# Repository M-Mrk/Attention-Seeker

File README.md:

# Attention-Seeker
## Overview
A multifunctional desk peripheral designed to display and alert you to notifications.

Attention-Seeker receives notifications from a companion app and displays them on its 2.8" color screen, with optional visual and audible alerts. It also features a rotary encoder and three mechanical keyboard switches for user input (no touch!).

In addition to notification-related features, it functions as a **clock**, **desk light**, and **macropad**.

### Why?
I often missed important notifications while zoning out or concentrating and also needed a desk light, so I built this.

### How?
- 2.8" TFT screen
- 3 mechanical keyboard switches
- Rotary encoder
- Rigid LED filament
- Buzzer
- ESP32-S3 DevKitC N16R8 CP2102
- Python companion app to run on a PC

### Example Use Cases
- **Notification:** Attention-Seeker buzzes, blinks, and displays the message.
- **Desk Light:** Toggle and dim the built-in LED for illumination.

## Features

### Notifications
Displays incoming notifications sent by the companion app with optional blinking or buzzing.

### Clock
- Displays time
- Synced via the companion app

### Macropad
- 6 hotkeys

### Navigation
- Mechanical keyboard switches for on-page actions
- Rotary encoder for switching between pages

### Other Features
- Dimmable desk light
- Buzzer for alerts

## Hardware

### MCU
The ESP32-S3 might be overkill but is ideal for handling the screen's pixel density, enabling fast page switching. Almost all pins are utilized, as the SPI interface for the screen consumes the majority of them.

### Lighting

#### LED Filament
The 3V filament draws about 100mA, requiring a 5V-to-3.3V LDO for power. An N-channel MOSFET drives the negative side of the LED filament.

#### Backlight
The backlight's current draw was uncertain during PCB design, so a transistor was added between it and the MCU for safety. This transistor is pulled high and can only be pulled low by the MCU.

### Other Components
All remaining components (switches, encoder, buzzer) are directly connected to the MCU.

# Build it yourself
## PCB
Order the PCB from the gerberfiles in [this zip](pcb/production/Attention-Seeker.zip). I would recommend black and the CAD files are designed for a 1.6mm thick pcb.

## Parts
Get/Order all parts from the [BOM](BOM.csv). I ordered them from reichelt and aliexpress and have included links for them. Watch out when buying the esp32 devkit, as there are countless versions and some even claim to be something different than they are.

## Soldering
First solder all smd components on the back, then the devkit and buzzer. Now you can solder on the screen based on your screen you might have to remove the sd card slot or cover it in kapton tape to be sure. I didnt have to shorten any pins, but you might have to. At last you can solder the LED on, but be very careful it snaps easily.

## Case
Print both the [top](case/case-top.3mf) and [bottom](case/case-bottom.3mf). If you dont have a cover for the rotary encoder you can also print [this](case/knob.3mf).

Place the pcb in the bottom and press fit the top on.

# Companion App
## Setup
Download [this folder](software/non-embedded/). 
Install the dependencys (if you want in a virtual environment)

`pip install -r requirements.txt`

Then just start the app
`python3 main.py`

## Device selection
Press refresh and it should automatically select your esp32. If not go through the drop down and select it manually.

## Time syncing
Press Sync Time

## Notifications
It will automatically send notifications to the device, but you can test it yourself. Press on the arrow to the left to extend the menu. Enter all your test informations and press Send JSON Notification. It should show up on the device and play a tone.

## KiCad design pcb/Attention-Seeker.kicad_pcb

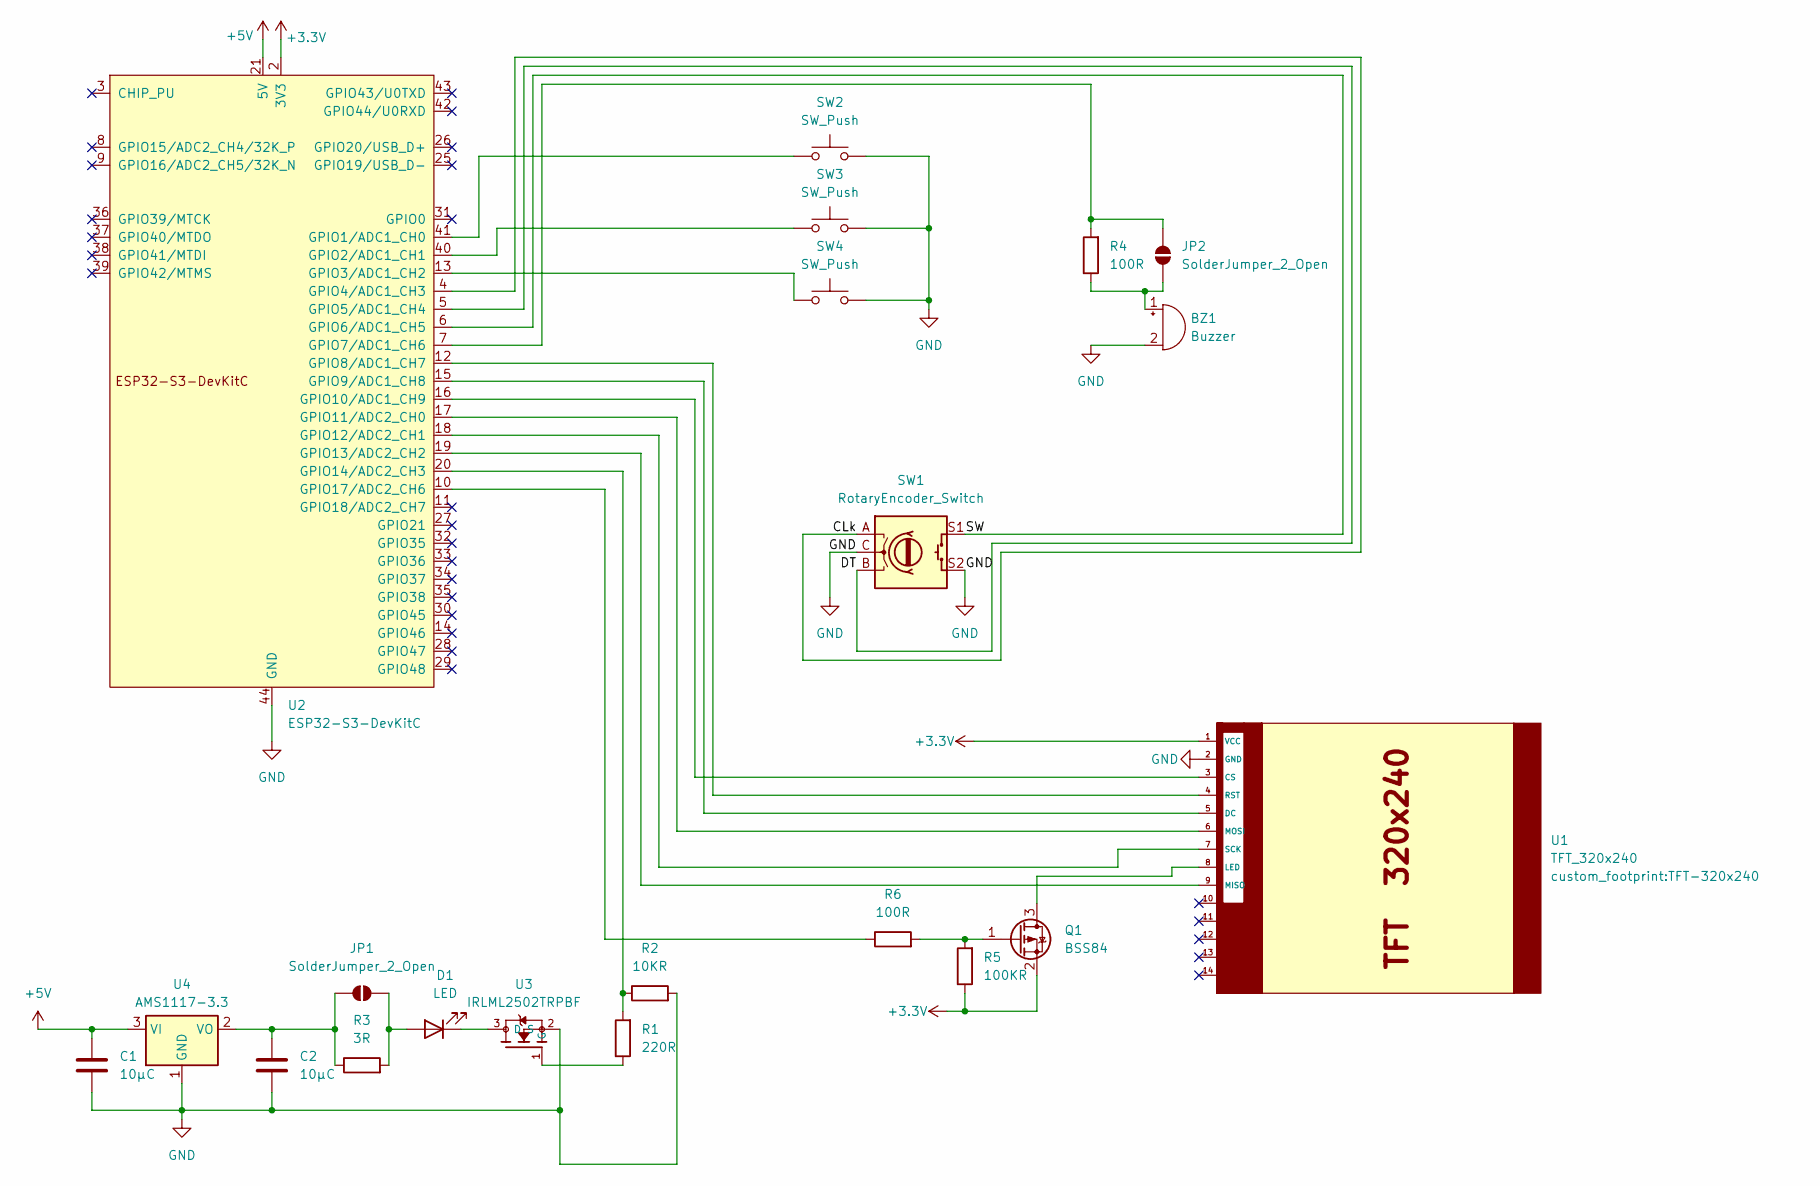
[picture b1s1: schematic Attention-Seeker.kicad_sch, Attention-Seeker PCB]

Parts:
BZ1: Buzzer; Buzzer_12x9.5RM7.6
C1, C2: 10µC; C_1206_3216Metric_Pad1.33x1.80mm_HandSolder
D1: LED; 38mm rigid LED filament
JP1, JP2: SolderJumper_2_Open; SolderJumper-2_P1.3mm_Open_Pad1.0x1.5mm
Q1: BSS84; SOT-23
R1: 220R; R_1206_3216Metric_Pad1.30x1.75mm_HandSolder
R2: 10KR; R_1206_3216Metric_Pad1.30x1.75mm_HandSolder
R3: 3R; R_1206_3216Metric_Pad1.30x1.75mm_HandSolder
R4, R6: 100R; R_1206_3216Metric_Pad1.30x1.75mm_HandSolder
R5: 100KR; R_1206_3216Metric_Pad1.30x1.75mm_HandSolder
SW1: RotaryEncoder_Switch; RotaryEncoder_Alps_EC11E-Switch_Vertical_H20mm
SW2, SW3, SW4: SW_Push; SW_Cherry_MX_1.00u_PCB
U1: TFT_320x240; TFT-320x240
U2: ESP32-S3-DevKitC
U3: IRLML2502TRPBF; SOT23
U4: AMS1117-3.3; SOT-223-3_TabPin2

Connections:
+3.3V: Q1.2 (S), R5.1, U1.1 (VCC), U2.1 (3V3), U2.2 (3V3)
+5V: C1.2, U2.21 (5V), U4.3 (VI)
/CLk: SW1.A, U2.4 (GPIO4/ADC1_CH3)
/DT: SW1.B, U2.5 (GPIO5/ADC1_CH4)
/SW: SW1.S1, U2.6 (GPIO6/ADC1_CH5)
GND: BZ1.2 (-), C1.1, C2.1, R2.2, SW1.C, SW1.S2, SW2.2, SW3.2, SW4.2, U1.2 (GND), U2.22 (GND), U2.23 (GND), U2.24 (GND), U2.44 (GND), U3.2 (S), U4.1 (GND)
unnamed: BZ1.1 (+), JP2.2 (B), R4.1
unnamed: D1.2 (A), JP1.2 (B), R3.2
unnamed: D1.1 (K), U3.3 (D)
unnamed: C2.2, JP1.1 (A), R3.1, U4.2 (VO)
unnamed: JP2.1 (A), R4.2, U2.7 (GPIO7/ADC1_CH6)
unnamed: Q1.3 (D), U1.8 (LED)
unnamed: Q1.1 (G), R5.2, R6.2
unnamed: U1.3 (CS), U2.16 (GPIO10/ADC1_CH9)
unnamed: U1.5 (DC), U2.15 (GPIO9/ADC1_CH8)
unnamed: U1.9 (MISO), U2.19 (GPIO13/ADC2_CH2)
unnamed: U1.6 (MOSI), U2.17 (GPIO11/ADC2_CH0)
unnamed: U1.4 (RST), U2.12 (GPIO8/ADC1_CH7)
unnamed: U1.7 (SCK), U2.18 (GPIO12/ADC2_CH1)
unnamed: SW2.1, U2.41 (GPIO1/ADC1_CH0)
unnamed: SW3.1, U2.40 (GPIO2/ADC1_CH1)
unnamed: SW4.1, U2.13 (GPIO3/ADC1_CH2)
unnamed: R1.2, R2.1, U2.20 (GPIO14/ADC2_CH3)
unnamed: R6.1, U2.10 (GPIO17/ADC2_CH6)
unnamed: R1.1, U3.1 (G)

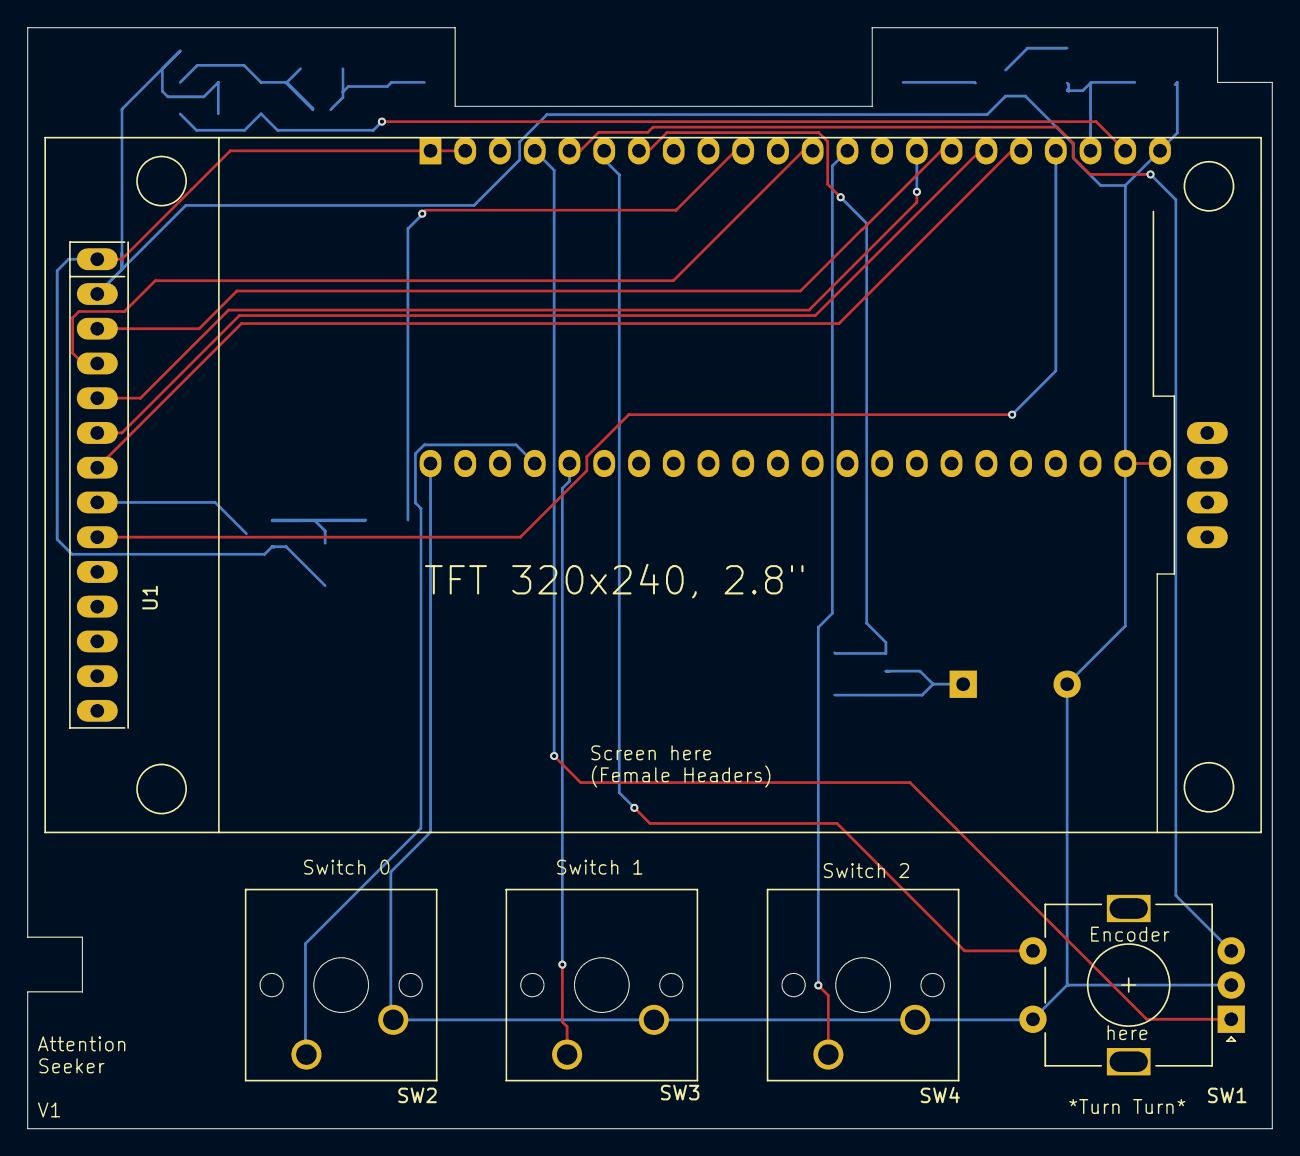
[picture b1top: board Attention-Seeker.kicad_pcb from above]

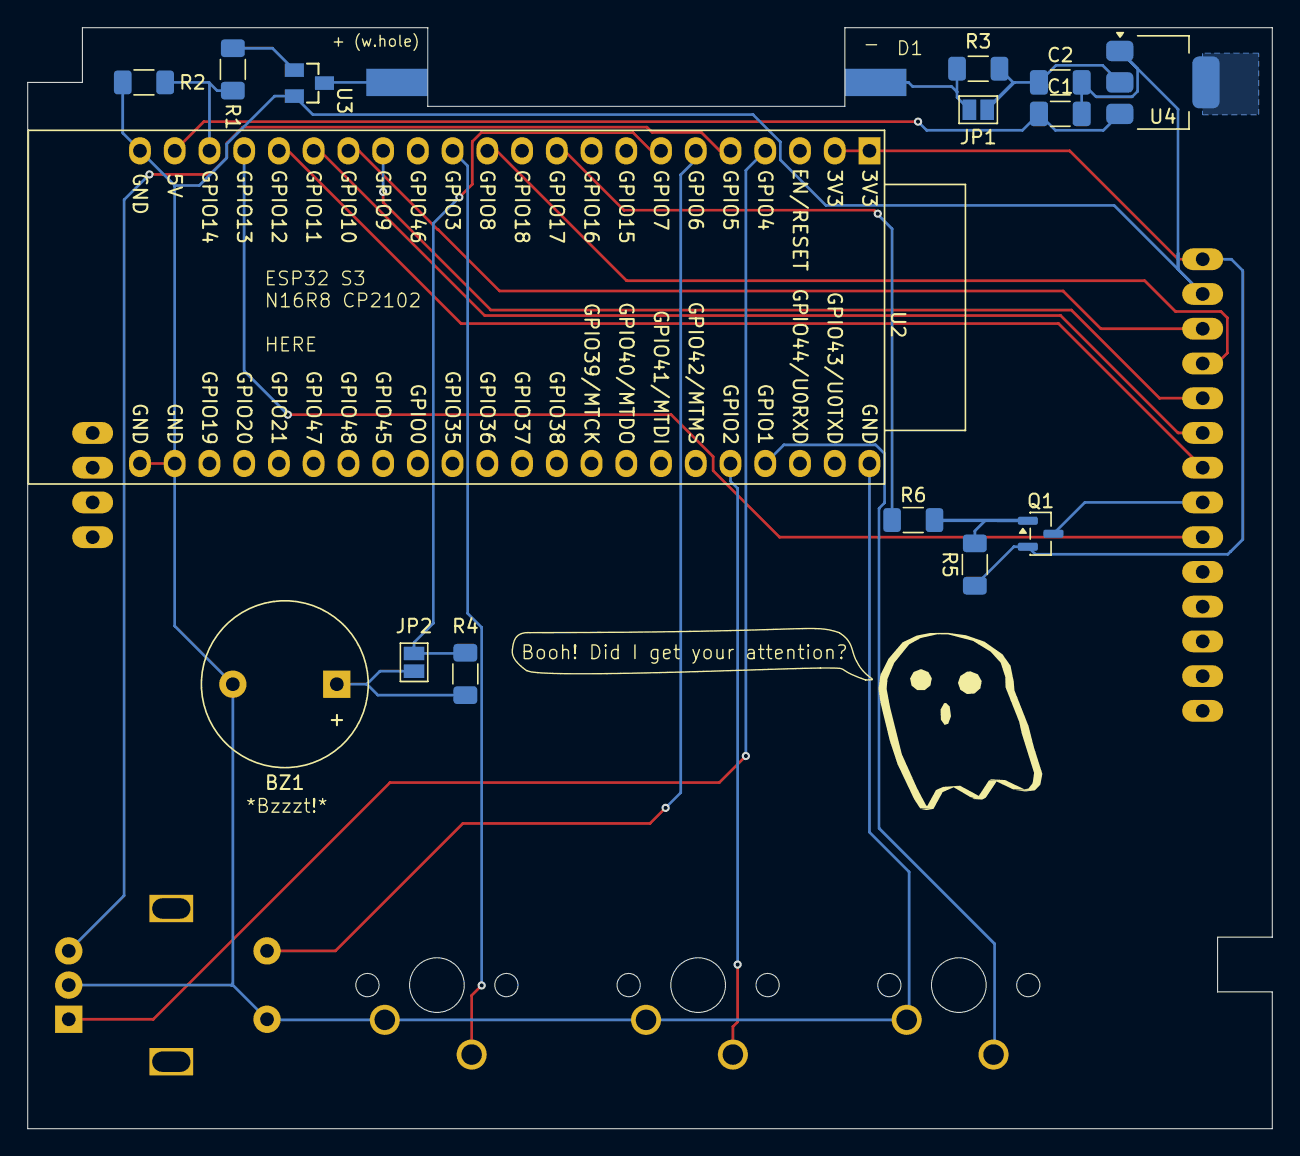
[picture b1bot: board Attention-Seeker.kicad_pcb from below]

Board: 2 copper layers, 91.0 x 80.5 mm, 21 parts (16 on the bottom side), 25 nets.

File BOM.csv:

Reference,Qty,Value,DNP,Exclude from BOM,Exclude from Board,Footprint,Datasheet,Price,Link Option,Link
U1,1,TFT_320x240,,,,custom_footprint:TFT-320x240,,"4,89€",without touch-2.8,https://de.aliexpress.com/item/1005006623369442.html
"SW2,SW3,SW4",3,SW_Push,,,,Button_Switch_Keyboard:SW_Cherry_MX_1.00u_PCB,~,"3,09€",10x Tactile Milk Tea,https://de.aliexpress.com/item/1005007052813358.html
"JP1,JP2",2,SolderJumper_2_Open,,Excluded from BOM,,Jumper:SolderJumper-2_P1.3mm_Open_Pad1.0x1.5mm,~,,,
SW1,1,RotaryEncoder_Switch,,,,Rotary_Encoder:RotaryEncoder_Alps_EC12E-Switch_Vertical_H20mm,~,"0,99€",,https://de.aliexpress.com/item/1005006582140027.html
/,3,Keycaps,,,Excluded from Board,None,,"2,35€",Orange/5pcs,https://de.aliexpress.com/item/1005008795444732.html
U3,1,IRLML2502TRPBF,,,,IRLML2502TRPBF:SOT23,,"0,25€",,https://www.reichelt.de/de/de/shop/produkt/mosfet_n-ch_20v_4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
U2,1,ESP32-S3-DevKitC,,,,Espressif:ESP32-S3-DevKitC,,"6,99€",N16R8 CP2102,https://de.aliexpress.com/item/1005007319706057.html
BZ1,1,Buzzer,,,,Buzzer_Beeper:Buzzer_12x9.5RM7.6,~,"1,25€",,https://de.aliexpress.com/item/1005006132874712.html
Q1,1,BSS84,,,,Package_TO_SOT_SMD:SOT-23,http://assets.nexperia.com/documents/data-sheet/BSS84.pdf,"0,05€",,https://www.reichelt.de/de/de/shop/produkt/mosfet_p-ch_-60v_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
U4,1,AMS1117-3.3,,,,Package_TO_SOT_SMD:SOT-223-3_TabPin2,http://www.advanced-monolithic.com/pdf/ds1117.pdf,"1,59€",AMS1117-3.3,https://de.aliexpress.com/item/1005002487704059.html
R3,1,3R,,,,Resistor_SMD:R_1206_3216Metric_Pad1.30x1.75mm_HandSolder,~,"0,02€",,https://www.reichelt.de/de/de/shop/produkt/smd-widerstand_12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
D1,1,38mm rigid LED filament,,,,custom_footprint:38mm rigid LED filament,~,"1,19€",2200K Warm Yellow/38mm DC3V 10pcs,https://de.aliexpress.com/item/1005007278852273.html
R1,1,220R,,,,Resistor_SMD:R_1206_3216Metric_Pad1.30x1.75mm_HandSolder,~,"0,02€",,https://www.reichelt.de/de/de/shop/produkt/smd-widerstand_12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
"C1, C2",2,10µC,,,,Capacitor_SMD:C_1206_3216Metric_Pad1.33x1.80mm_HandSolder,~,"0,08€",,https://www.reichelt.de/de/de/shop/produkt/mlcc_1206_10_f_25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
R2,1,10KR,,,,Resistor_SMD:R_1206_3216Metric_Pad1.30x1.75mm_HandSolder,~,"0,02€",,https://www.reichelt.de/de/de/shop/produkt/smd-widerstand_12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
"R4,R6",2,100R,,,,Resistor_SMD:R_1206_3216Metric_Pad1.30x1.75mm_HandSolder,~,"0,04€",,https://www.reichelt.de/de/de/shop/produkt/smd-widerstand_12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
R5,1,100KR,,,,Resistor_SMD:R_1206_3216Metric_Pad1.30x1.75mm_HandSolder,~,"0,08€",,https://www.reichelt.de/de/de/shop/produkt/mlcc_1206_10_f_25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
PCB (JLCPCB),5,PCB,,,Excluded from Board,None,,"4,70€","LeadFree HASL, Black(no price change)",

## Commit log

2025-10-09 first version of schematic
2025-10-13 finished v1 of pcb
2025-10-13 Updated README. Added BOM and 3d Model
2025-10-13 Fixed pictures in README
2025-10-13 Updated Readme, gerber and added pcb price to BOM
2025-10-13 moved BOM.csv to root for blueprint requirements
2025-10-13 Added banner image
2025-10-14 changed pads for MCU and screen to fit square pins, 1mm hole diameter. Found cheaper MCU alternative. Moved MCU more to the edge and rerouted accordingly.
2025-10-14 Fixed some routing weirdness (unessecary paths) and added nearly fitting model for the mcu. Updated pictures and 3d Model
2025-10-14 updated .gitignore to ignore temporary kicad edit files
2025-10-15 Added V1 of case, added assembly.md and reference to it in readme
2025-10-16 redid the case pictures without grid and refactored the README
2025-10-16 updated rotary encoder footprint and sourced smd parts from other source
2025-10-17 base companion app layout
2025-10-24 fixed critical issue with cap alignment
2025-11-08 created platformio project, tested screen and created pins header
2025-11-08 basic displayManager patterns and layout
2025-11-11 switched to TFT_eSPI and improved display manager
2025-11-12 implemented checking for input
2025-11-12 implemented settings screen to control screen brightness
2025-11-13 implemented error screen
2025-11-15 implemented melodymanager
2025-12-28 added serial communication and added notification/time methods on both ends
2025-12-28 Add LightManager for controlling light levels and integrate with SettingsScreen
2025-12-28 Notification now also blinks light
2026-01-01 Notification menu now wraps text correctly and updated ReadMe
2026-01-24 Added more information to the README
